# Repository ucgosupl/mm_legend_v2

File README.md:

# Legend v2 - the micromouse robot

master: 

dev: 

The purpose of micromouse robot is to find path in the labirynth. To accomplish this task, robot should control its motors, detect walls using distance sensors and run pathfinding alhorithms.

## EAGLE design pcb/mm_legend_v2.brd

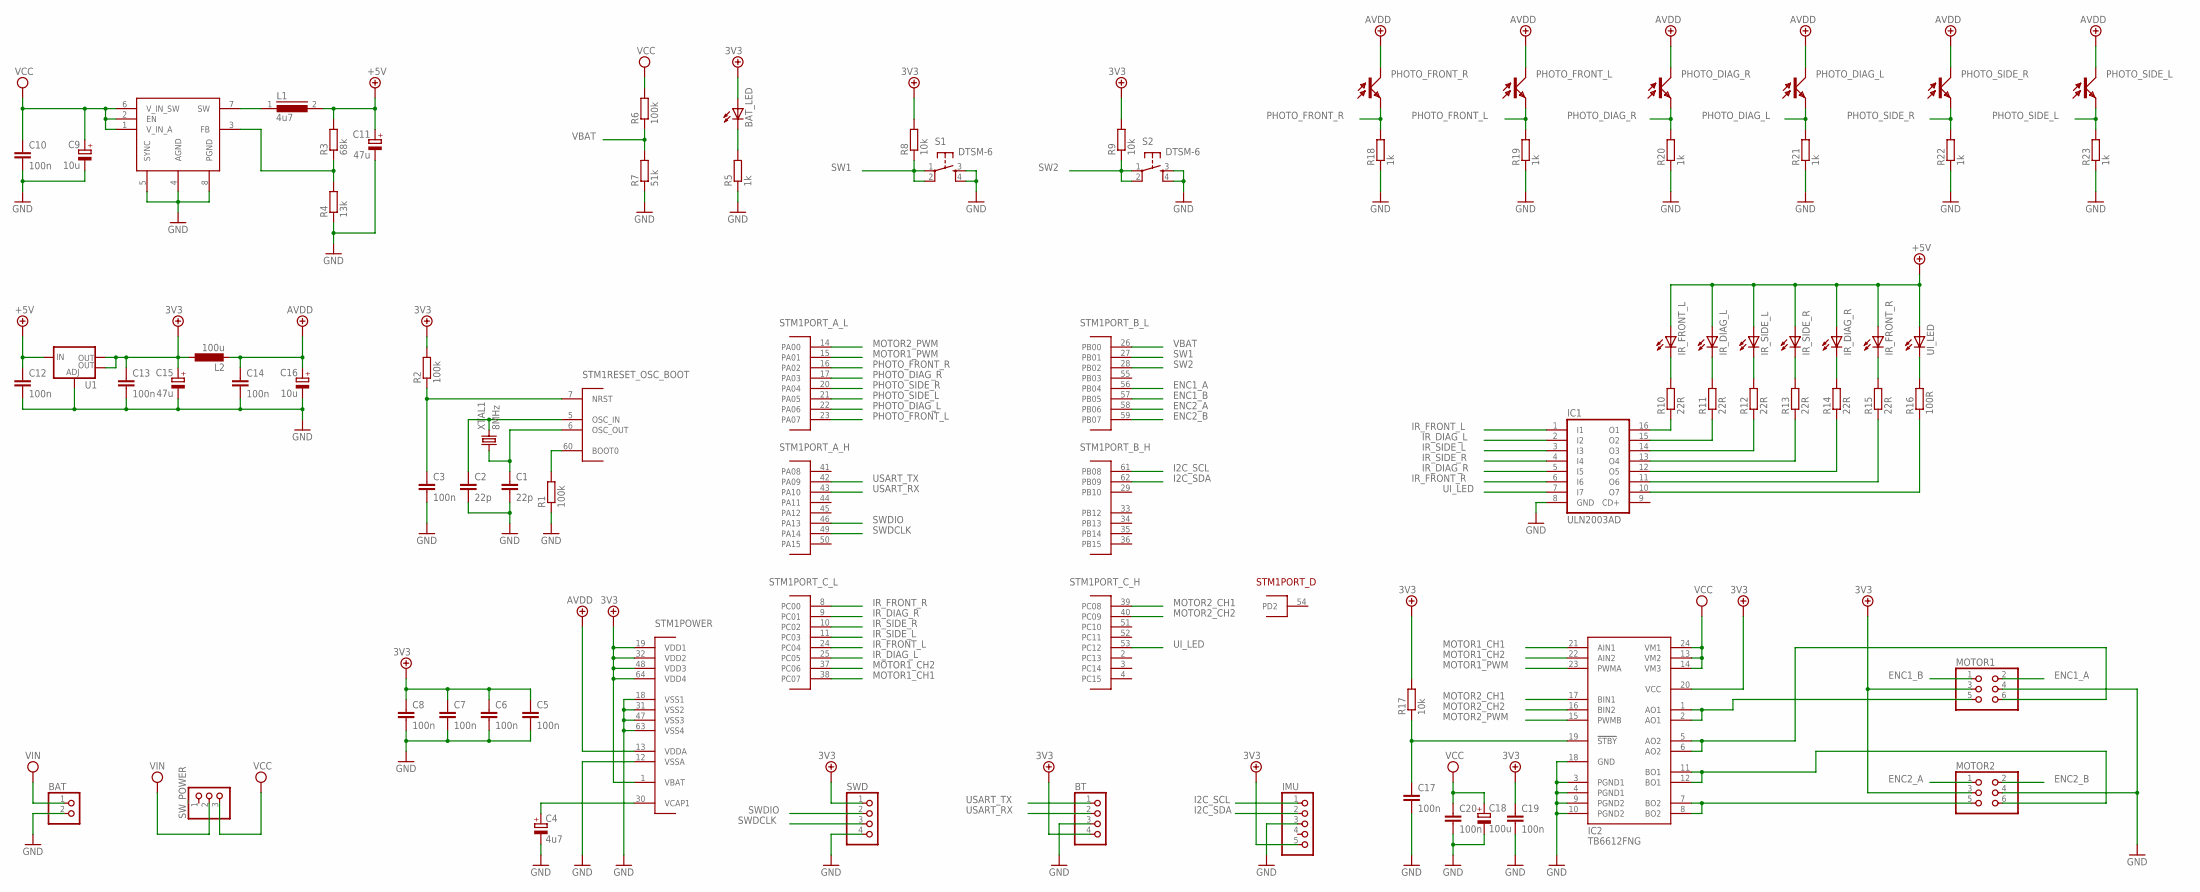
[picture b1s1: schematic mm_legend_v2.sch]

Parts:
BAT: PINHD-1X2; 1X02
BAT_LED: LEDCHIP-LED0805; CHIP-LED0805
BT: PINHD-1X4; 1X04
C1, C2: 22p; C0805K
C3, C5, C6, C7, C8, C10, C12, C13, C14, C17, C19, C20: 100n; C0805K
C4: 4u7; A/3216-18R
C9, C16: 10u; A/3216-18R
C11, C15: 47u; B/3528-21W
C18: 100u; C/6032-28R
IC1: ULN2003AD; SO16
IC2: TB6612FNG; SSOP24
IMU: PINHD-1X5; 1X05
IR_DIAG_L: LED5MM
IR_DIAG_R: LED5MM
IR_FRONT_L: LED5MM
IR_FRONT_R: LED5MM
IR_SIDE_L: LED5MM
IR_SIDE_R: LED5MM
L1: 4u7; DR74
L2: 100u; L1812
MOTOR1, MOTOR2: PINHD-2X3; 2X03
PHOTO_DIAG_L: PHOTO_TRANSISTOR_5MM; 5MM
PHOTO_DIAG_R: PHOTO_TRANSISTOR_5MM; 5MM
PHOTO_FRONT_L: PHOTO_TRANSISTOR_5MM; 5MM
PHOTO_FRONT_R: PHOTO_TRANSISTOR_5MM; 5MM
PHOTO_SIDE_L: PHOTO_TRANSISTOR_5MM; 5MM
PHOTO_SIDE_R: PHOTO_TRANSISTOR_5MM; 5MM
R1, R2, R6: 100k; R0805W
R3: 68k; R0805W
R4: 13k; R0805W
R5, R18, R19, R20, R21, R22, R23: 1k; R0805W
R7: 51k; R0805W
R8, R9, R17: 10k; R0805W
R10, R11, R12, R13, R14, R15: 22R; R0805W
R16: 100R; R0805W
S1, S2: DTSM-6
STM1: STM32F401RB; LQFP64
SWD: PINHD-1X4; 1X04
SW_POWER: PINHD-1X3; 1X03
U1: V_REG_LM1117SOT223; SOT223
U$2: ST1S10PHR; SO8
UI_LED: LEDCHIP-LED0805; CHIP-LED0805
XTAL1: 8MHz; SMD_50X32

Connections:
3V3: BAT_LED.A, BT.4, C5.1, C6.1, C7.1, C8.1, C13.1, C15.+, C19.1, IC2.20 (VCC), IMU.5, L2.1, MOTOR1.3, MOTOR2.3, R2.2, R8.2, R9.2, R17.2, STM1.1 (VBAT), STM1.19 (VDD1), STM1.32 (VDD2), STM1.48 (VDD3), STM1.64 (VDD4), SWD.1, U1.2 (OUT), U1.4 (OUT)
+5V: C11.+, C12.1, IR_DIAG_L.A, IR_DIAG_R.A, IR_FRONT_L.A, IR_FRONT_R.A, IR_SIDE_L.A, IR_SIDE_R.A, L1.2, R3.2, U1.3 (IN), UI_LED.A
AVDD: C14.1, C16.+, L2.2, PHOTO_DIAG_L.C, PHOTO_DIAG_R.C, PHOTO_FRONT_L.C, PHOTO_FRONT_R.C, PHOTO_SIDE_L.C, PHOTO_SIDE_R.C, STM1.13 (VDDA)
ENC1_A: MOTOR1.2, STM1.56 (PB04)
ENC1_B: MOTOR1.1, STM1.57 (PB05)
ENC2_A: MOTOR2.1, STM1.58 (PB06)
ENC2_B: MOTOR2.2, STM1.59 (PB07)
GND: BAT.2, BT.3, C1.2, C2.2, C3.2, C4.-, C5.2, C6.2, C7.2, C8.2, C9.-, C10.2, C11.-, C12.2, C13.2, C14.2, C15.-, C16.-, C17.2, C18.-, C19.2, C20.2, IC1.8 (GND), IC2.3 (PGND1), IC2.4 (PGND1), IC2.9 (PGND2), IC2.10 (PGND2), IC2.18 (GND), IMU.3, MOTOR1.4, MOTOR2.4, R1.1, R4.1, R5.1, R7.1, R18.1, R19.1, R20.1, R21.1, R22.1, R23.1, S1.3, S1.4, S2.3, S2.4, STM1.12 (VSSA), STM1.18 (VSS1), STM1.31 (VSS2), STM1.47 (VSS3), STM1.63 (VSS4), SWD.4, U1.1 (ADJ), U$2.4 (AGND), U$2.5 (SYNC), U$2.8 (PGND)
I2C_SCL: IMU.1, STM1.61 (PB08)
I2C_SDA: IMU.2, STM1.62 (PB09)
IR_DIAG_L: IC1.2 (I2), STM1.25 (PC05)
IR_DIAG_R: IC1.5 (I5), STM1.9 (PC01)
IR_FRONT_L: IC1.1 (I1), STM1.24 (PC04)
IR_FRONT_R: IC1.6 (I6), STM1.8 (PC00)
IR_SIDE_L: IC1.3 (I3), STM1.11 (PC03)
IR_SIDE_R: IC1.4 (I4), STM1.10 (PC02)
MOTOR1_CH1: IC2.21 (AIN1), STM1.38 (PC07)
MOTOR1_CH2: IC2.22 (AIN2), STM1.37 (PC06)
MOTOR1_PWM: IC2.23 (PWMA), STM1.15 (PA01)
MOTOR2_CH1: IC2.17 (BIN1), STM1.39 (PC08)
MOTOR2_CH2: IC2.16 (BIN2), STM1.40 (PC09)
MOTOR2_PWM: IC2.15 (PWMB), STM1.14 (PA00)
unnamed: R1.2, STM1.60 (BOOT0)
unnamed: C3.1, R2.1, STM1.7 (NRST)
unnamed: C1.1, STM1.6 (OSC_OUT), XTAL1.1
unnamed: C2.1, STM1.5 (OSC_IN), XTAL1.2
unnamed: BAT_LED.C, R5.2
unnamed: C17.1, IC2.19 (!STBY), R17.1
unnamed: R16.2, UI_LED.C
unnamed: IR_FRONT_L.K (C), R10.2
unnamed: C4.+, STM1.30 (VCAP1)
unnamed: IR_DIAG_L.K (C), R11.2
unnamed: IR_SIDE_L.K (C), R12.2
unnamed: IR_SIDE_R.K (C), R13.2
unnamed: IR_DIAG_R.K (C), R14.2
unnamed: IR_FRONT_R.K (C), R15.2
unnamed: IC1.16 (O1), R10.1
unnamed: IC1.15 (O2), R11.1
unnamed: IC1.14 (O3), R12.1
unnamed: IC1.13 (O4), R13.1
unnamed: IC1.12 (O5), R14.1
unnamed: IC1.11 (O6), R15.1
unnamed: IC1.10 (O7), R16.1
unnamed: L1.1, U$2.7 (SW)
unnamed: IC2.1 (AO1), IC2.2 (AO1), MOTOR1.5
unnamed: IC2.5 (AO2), IC2.6 (AO2), MOTOR1.6
unnamed: R3.1, R4.2, U$2.3 (FB)
unnamed: IC2.11 (BO1), IC2.12 (BO1), MOTOR2.6
unnamed: IC2.7 (BO2), IC2.8 (BO2), MOTOR2.5
PHOTO_DIAG_L: PHOTO_DIAG_L.E, R21.2, STM1.22 (PA06)
PHOTO_DIAG_R: PHOTO_DIAG_R.E, R20.2, STM1.17 (PA03)
PHOTO_FRONT_L: PHOTO_FRONT_L.E, R19.2, STM1.23 (PA07)
PHOTO_FRONT_R: PHOTO_FRONT_R.E, R18.2, STM1.16 (PA02)
PHOTO_SIDE_L: PHOTO_SIDE_L.E, R23.2, STM1.21 (PA05)
PHOTO_SIDE_R: PHOTO_SIDE_R.E, R22.2, STM1.20 (PA04)
SW1: R8.1, S1.1, S1.2, STM1.27 (PB01)
SW2: R9.1, S2.1, S2.2, STM1.28 (PB02)
SWDCLK: STM1.49 (PA14), SWD.3
SWDIO: STM1.46 (PA13), SWD.2
UI_LED: IC1.7 (I7), STM1.53 (PC12)
USART_RX: BT.2, STM1.43 (PA10)
USART_TX: BT.1, STM1.42 (PA09)
VBAT: R6.1, R7.2, STM1.26 (PB00)
VCC: C9.+, C10.1, C18.+, C20.1, IC2.13 (VM2), IC2.14 (VM3), IC2.24 (VM1), R6.2, SW_POWER.3, U$2.1 (V_IN_A), U$2.2 (EN), U$2.6 (V_IN_SW)
VEE: BAT.1, SW_POWER.2

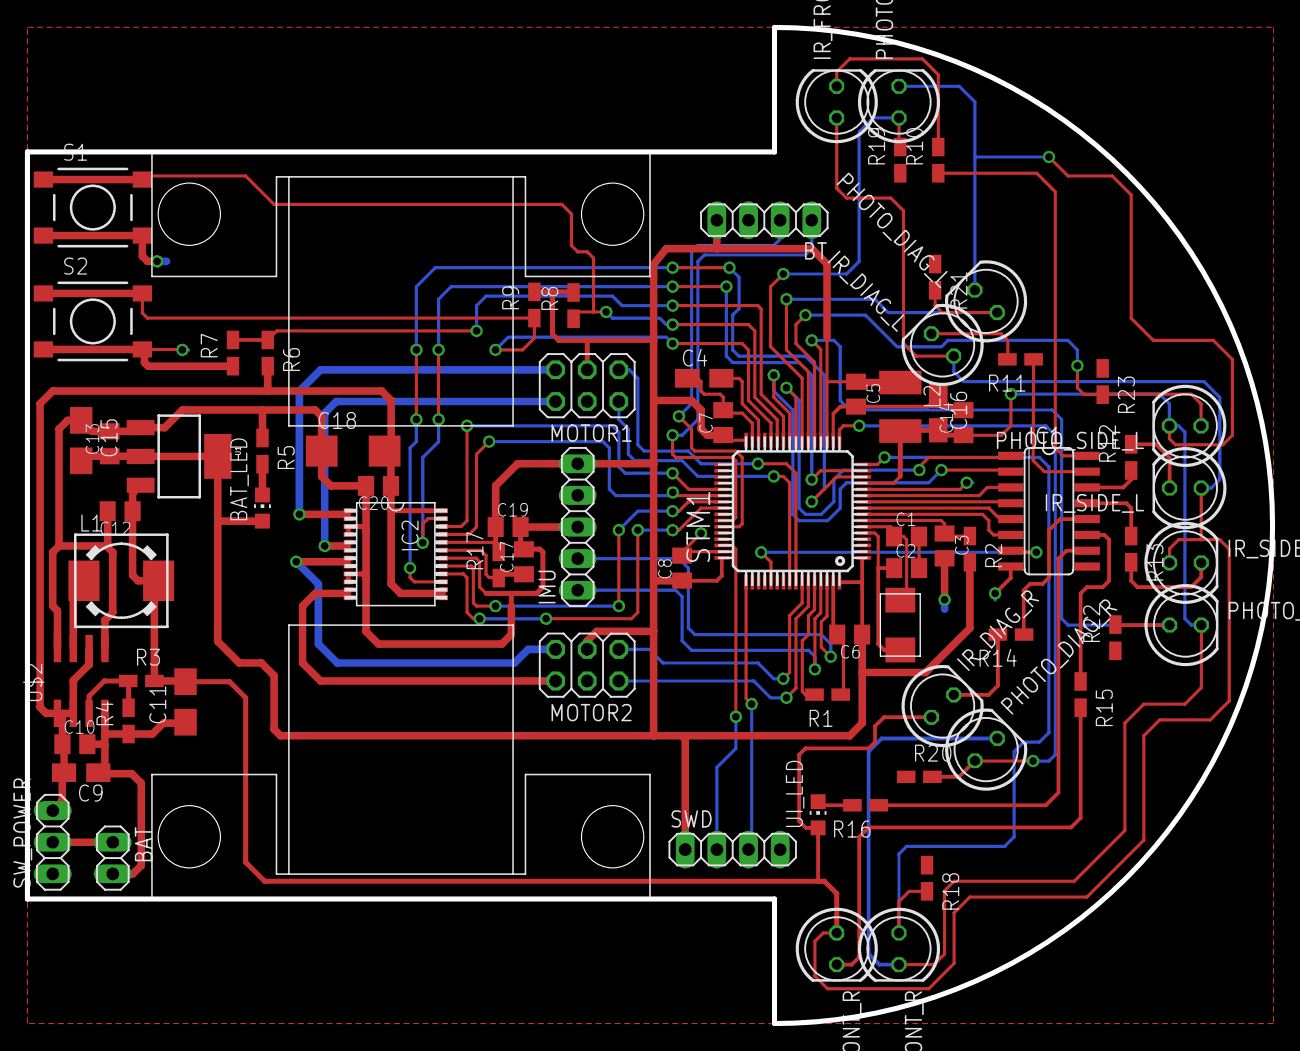
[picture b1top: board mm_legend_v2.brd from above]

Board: 2 copper layers, 100.0 x 80.0 mm, 76 parts (0 on the bottom side), 65 nets.

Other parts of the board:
U$1, U$3: MOTOR_HOLDER

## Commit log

2017-03-04 project: initial commit.
    Added gitignore, license and readme.
2017-03-05 pcb: added circuit diagram.
2017-03-13 pcb: added library parts used for circuit and pcb.
2017-03-13 pcb: created pcb design.
2017-03-18 pcb: minor changes in pcb and schematic.
2017-03-18 pcb: redesigned pcb.
2017-03-26 project: added project template with FreeRTOS.
2017-03-26 project: added cpputest unit test framework.
2017-04-09 project: added travis-ci script.
    Added first test version of the script. It tries to run make all using tools installed by default.
2017-04-16 project: added installing bleeding edge toolchain to travis-ci configuration.
2017-04-22 project: updated travis script to be not depended on exact toolchain version.
2017-05-03 led: added prototypes for led driver functions.
2017-05-03 adc: added prototypes for ADC driver functions.
2017-05-03 photo: added prototypes for phototransistor module functions.
2017-05-03 vbat: added prototypes for battery monitor functions.
2017-05-03 wall: added prototypes for wall detection module functions.
2017-05-03 hbridge: added prototypes for H-bridge module functions.
2017-05-03 encoder: added prototypes for encoder driver functions.
2017-05-03 pid: added prototypes for PID controller functions.
2017-05-03 motor: added prototypes for motor control module functions.
2017-05-03 i2c: added prototypes for I2C master driver.
2017-05-03 imu: added prototypes for IMU sensors module functions.
2017-05-09 usart: added prototypes for USART driver functions.
2017-05-09 logger: added prototypes for logger module functions.
2017-05-09 console: added prototypes for debug console functions.
2017-05-13 button: added prototypes for button driver functions.
2017-05-13 user_interface: added prototypes for user interface functions.
2017-05-13 hbridge: implemented H-bridge driver and hardware test.
2017-05-29 core: fixed wrong bus frequency definitions.
2017-05-29 usart: implemented usart Rx functionality.
2017-05-29 console: implemented console task.
2017-07-02 proj: move common includes to platform_specific.h.
2017-07-02 usart: add implementation of usart Tx.
    USART Tx is implemented using DMA.
    HW test target - logger - is created.
2017-07-02 logger: add logger implementation and connect it with system printf.
2017-07-25 proj: update travis-ci script to fix issue #3
2017-07-26 hw_test: added motor_ident hw_test target.
2017-07-26 button: add button driver implementation.
2017-07-26 encoder: add encoder implementation
2017-07-26 data: gather motor identification data - issue #3
2017-07-28 data: create script for motor identification - refers to #4
2017-08-08 data: create matlab scripts for processing motor ident data - refers to #4.
2017-09-04 pid: add pid controller implementation.
2017-09-04 motor: add motor task implementation.
2017-09-04 data: update gathered data and matlab scripts with new data.
2017-09-04 hw_test: add motor linear regulation test.
2017-09-04 proj: add to readme file build status from travis-ci.
2017-09-04 hw_test: add imu test template.
2017-09-06 imu: add i2c driver and imu task.
2017-09-13 proj: fix travis build errors
2017-09-15 hw_test/motor_linear: fixed header comments.
2017-09-24 pcb: update pcb and schematic.
    Changes:
    - Moved BT connector away from motor holder.
    - Changed pinout of motor connectors - fix issue #1.
    - Added thicker lines for motor + and - signals.
2017-10-22 pcb: updated vbat resistors to real values.
    Until now resistor values were 20k and 100k. 20k resistor doesn't exist in the series.
2017-10-22 motor: update forward and backward functions for new motor orientation.
2017-10-22 encoder: adjust encoder measurements to return positive values when moving forward.
2017-10-22 motor: calculate new PID settings for linear movement.
2017-10-23 imu: add initial delay to imu task to allow sensor to power up.
2017-10-23 hw_test/motor_ident: adapt for angular velocity.
2017-10-29 imu: change gyro and accelerometer sampling frequency.
    High sample frequency caused higher exposure to noise generated by mechanical vibration caused by motors.
2017-11-18 hbridge: increase motor power resolution from 100 to 1000.
2017-11-18 motor: change function return values to float in api functions.
2017-11-18 data: gather data for angular velocity controller.
2017-11-18 scripts: create script and simulink model for angular velocity controller tuning.
2017-11-18 motor: implement angular velocity controller.
    Also added tools for angular controller tests in hw test target motor_linear.
2017-11-18 proj: add changelog.
2017-11-18 scripts: update simulink model for angular velocity controller.
2017-11-18 proj: fix github links in changelog.
2017-12-03 scripts: add plot axis descriptions to ident_angular script.
2017-12-03 matrix: add external matrix library based on libfixmatrix.
2017-12-07 position: add position estimator implementation.
2017-12-07 motor: update angular controller to use correct orientation angle.
2017-12-13 position: fix bugs with position estimation.
    Changes:
    - Ticks per motor cycle now accounts for encoder rising/falling edge on both channels A and B
    - Angular velocity from gyroscope is counted backwards compared to orientation angle
    - Angular velocity from encoders are measured in radians, conversion to degrees is necessary
2017-12-20 imu: add hw test for imu sensor initial states after power up.
    After power up first few gyro samples are bogus. Added delay to remove this effect.
2017-12-21 position: add gyro bias estimation.
2017-12-22 position: modify initial gyro estimation
2017-12-22 proj: update changelog.
2018-01-21 led: add led driver implementation.
2018-01-21 wall: add led handling to wall task.
2018-01-22 hw_test: add wall sensor hw test.
2018-01-22 adc: add ADC implementation.
2018-02-03 vbat: vbat task implementation.
    Implementation checked using unit tests.
2018-02-04 vbat: add vbat check to wall task.
2018-02-04 vbat: fix bug with wrong ADC read values for vbat channel.
    The reason was not enabled GPIO port for VBAT. All other ADC channels were on GPIOA only vbat on GPIOB.
2018-02-04 hw_test: add vbat to every hw test.
2018-02-04 vbat: update battery discharge threshold.
    Threshold set to 7V after analysing lipol discharge characteristics.
2018-02-05 wall: gather wall sensor measurements.
2018-02-05 wall: conversion between adc values and distance.
2018-02-07 scripts: add script for wall sensor identification.
2018-02-07 wall: update lookup table with more accurate approximation.
2018-02-09 project: add incremental build option for main and hw_test.
2018-02-09 project: add incremental build for unit tests.
2018-02-12 pcb: fix motor connector wiring.
    Fix issue #1.
2018-02-12 pcb: reroute paths to h-bridge around imu sensor.
    Fixes issue #6.
2018-02-12 pcb: move status led to the front.
2018-02-13 pcb: change wall sensor placement.
    Fixes #7.
2018-02-13 wall: minor change.
2018-02-14 project: update changelog.
2018-03-05 map: implement labirynth map module.
2018-03-06 solver: prototype implementation of maze solver.
    Handling mazetool in unit tests to read mazes from the file and load to map.
2018-03-06 solver: fix failing mazetool test.
    Mazetool tests are used only as framework to run solver on existing maze files. These are not real tests.
2018-03-21 wall: implement measurements for all sensors.
2018-03-21 scripts: add generate lookups script creating c array for every sensor.
2018-03-21 wall: separate lookup table for every sensor.
2018-03-22 wall: update naming of sensors in code and scripts.
2018-03-22 wall: refactor wall sensor task.
2018-03-24 wall_sensor: change module name from wall to wall_sensor.
    Need to distinguish between wall_sensor and wall_detection.
2018-03-24 wall_detection: add unit test build.
2018-03-24 wall_detection: implement cell calculation based on position.
2018-03-29 wall_detection: change unit tests names.
2018-03-29 map_update: move calculate cell function to map update module.
2018-03-29 wall_detection: add sensor position calculation.
    Sensor position is shifted from robot reference point by some offset. Position of every sensor is calculated so position of wall detected by them could be estimated more precisely. Closes #8.
2018-03-29 wall_detection: add more unit tests.
2018-03-29 wall_detection: add wall position calculation.
2018-03-29 map: add map validate for state present.
    Map validate module checks if number of detections of a wall reached threshold and it could be added to map.
2018-03-29 map: implement logic for adding detected no walls.
2018-03-29 map: change map orientation so x and y cell indices grows in the same directions as coordinates.
2018-03-29 map: map_update functions now calls map validate, not wall add directly.
2018-03-29 map: update code documentation.
2018-03-29 map: add validate detection for state absent.
2018-03-29 map: update documentation.
2018-03-29 map: implement logic for adding detected wall present.
2018-03-29 mazetool: fix printing laibrynth layouts.
2018-04-08 map: fix warning with not initialized functions.
2018-04-08 solver: add new functions for calculating paths to the center or to the start and returning next cell index.
2018-04-08 search: implement search run state machine.
2018-04-08 search: update documentation.
2018-04-09 map: add functions for adjacent cell calculation, update map_validate counters for both sides of the wall.
    Closes #13.
2018-04-10 unit_test: add mock templates, update mocks for search module.
    References #14.
2018-04-10 unit_tests: update mocks for unit tests.
2018-06-29 motor: update pid controller.
    Now PID regulator depends on last value of u(t).
    Updated tuning parameters - lower values are needed with new PID calculation.
    Removed dependency on imu from motor_linear hardware test.
2018-07-12 scripts: update scripts for identification of angular velocity.
2018-07-12 vbat: decrease battery undervoltage threshold.
2018-07-12 data: add measurement data for angular velocity.
2018-07-12 motor: fix motor controller.
    Changes:
    - Single forward velocity controller instead left and right.
    - Angular velocity controller uses encoders instead of gyro.
    - Angular set val given in angle and calculated to ticks.
    - Tune angluar PID.
    - Temporarily remove motor control signal lower bound.
2018-07-12 hw_test: update motor linear test.
    Changes:
    - Update set values for forward and angular velocity.
    - Rename encoder data to wheel data as this value is velocity in mm/Ts not ticks.
    - Print wheel data and control signal instead of gyro.
2018-07-17 motor: remove motor control offset.
2018-07-17 data: remove old data files.
2018-07-17 scripts: update python identification script.
2018-07-18 script: update simulink model for closed loop angular.
    Changes:
    - Add transport delay.
    - Update transfer function.
2018-07-18 motor: fix converting velocity from mm and deg to ticks.
2018-07-18 motor: update angular pid tuning.
2018-07-18 scripts: update simulink model for closed loop linear.
2018-07-18 motor: update linear velocity set calculation.
2018-07-19 motor: update linear velocity pid tuning.
2018-07-19 motor: fix motor control for forward velocity.
2018-07-19 pid: fix anti-windup bound.
2018-07-19 motor: fix formatting.
2018-07-19 hw_test: update motor_linear test.
2018-07-19 motor: add pid state resetting.
    Pid state could be reset when not moving to remove effect of integral term error cumulating when control is off.
2023-05-24 usart: change baudrate to 9600
2023-05-25 button: change pins to PB03 and PB04

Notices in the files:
parts and their libraries:
SparkFun-PowerIC: Licensing: Creative Commons ShareAlike 4.0 International - https://creativecommons.org/licenses/by-sa/4.0
